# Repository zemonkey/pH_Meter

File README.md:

# pH_Meter
 A pH Meter with very low input current using LMP7721

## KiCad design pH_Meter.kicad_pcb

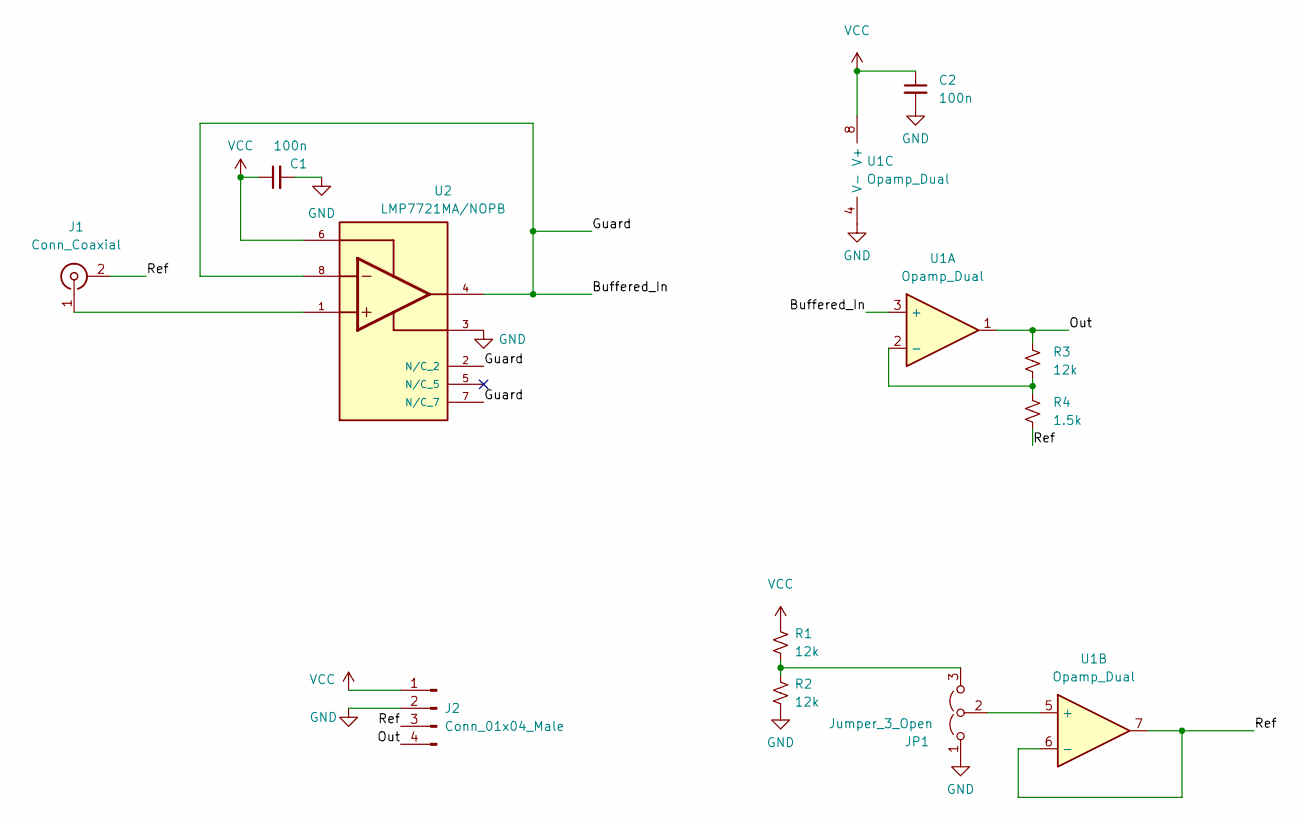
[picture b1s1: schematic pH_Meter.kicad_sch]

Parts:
C1, C2: 100n; C_0805_2012Metric_Pad1.18x1.45mm_HandSolder
J1: Conn_Coaxial; BNC_Amphenol_B6252HB-NPP3G-50_Horizontal
J2: Conn_01x04_Male; PinSocket_1x04_P2.54mm_Vertical
JP1: Jumper_3_Open; PinSocket_1x03_P2.54mm_Vertical
R1, R2, R3: 12k; R_0805_2012Metric_Pad1.20x1.40mm_HandSolder
R4: 1.5k; R_0805_2012Metric_Pad1.20x1.40mm_HandSolder
U1: Opamp_Dual; MSOP-8_3x3mm_P0.65mm
U2: LMP7721MA/NOPB; SOIC-8_3.9x4.9mm_P1.27mm; PARTREV E

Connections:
/Buffered_In: U1.3 (+), U2.2 (N/C), U2.4, U2.7 (N/C), U2.8
/Out: J2.4, R3.1, U1.1
/Ref: J1.2 (Ext), J2.3, R4.2, U1.6 (-), U1.7
GND: C1.2, C2.2, J2.2, JP1.1 (A), R2.2, U1.4 (V-), U2.3
unnamed: J1.1 (In), U2.1
unnamed: JP1.2 (C), U1.5 (+)
unnamed: JP1.3 (B), R1.2, R2.1
unnamed: R3.2, R4.1, U1.2 (-)
VCC: C1.1, C2.1, J2.1, R1.1, U1.8 (V+), U2.6

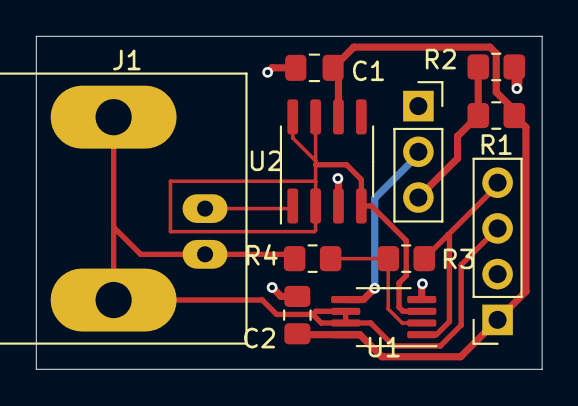
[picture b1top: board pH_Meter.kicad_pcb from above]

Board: 2 copper layers, 28.1 x 18.5 mm, 11 parts (0 on the bottom side), 9 nets.

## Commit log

2022-06-14 I forgot to remove the PCB mask layer
